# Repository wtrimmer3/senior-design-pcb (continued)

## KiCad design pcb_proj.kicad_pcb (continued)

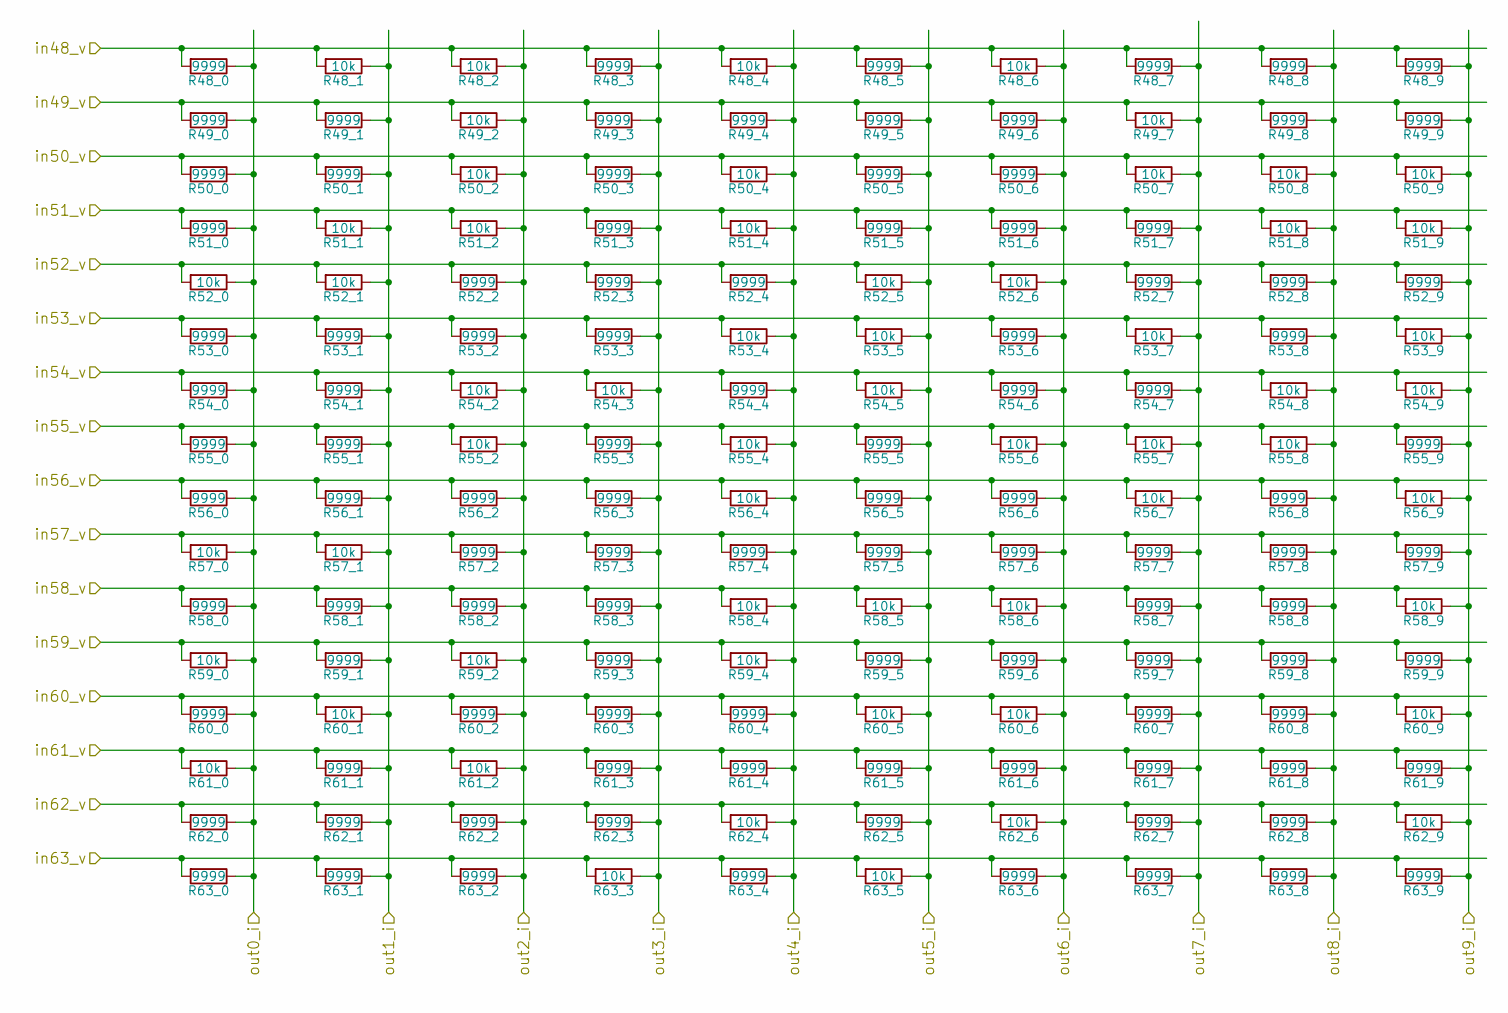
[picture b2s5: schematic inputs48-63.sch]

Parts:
R48_0, R48_3, R48_5, R48_7, R48_8, R48_9, R49_0, R49_1, R49_3, R49_4, R49_5, R49_6, R49_8, R49_9, R50_0, R50_1, R50_3, R50_5, R50_6, R51_0, R51_3, R51_5, R51_6, R51_7, R52_2, R52_3, R52_4, R52_7, R52_8, R52_9, R53_0, R53_1, R53_2, R53_3, R53_6, R53_8, R54_0, R54_1, R54_4, R54_6, R54_7, R55_0, R55_1, R55_3, R55_5, R55_9, R56_0, R56_1, R56_2, R56_3, R56_5, R56_6, R56_8, R57_2, R57_3, R57_4, R57_5, R57_6, R57_7, R57_8, R57_9, R58_0, R58_1, R58_2, R58_3, R58_7, R58_8, R59_1, R59_3, R59_5, R59_6, R59_7, R59_8, R59_9, R60_0, R60_2, R60_3, R60_4, R60_7, R60_8, R61_1, R61_3, R61_4, R61_5, R61_6, R61_7, R61_8, R61_9, R62_0, R62_1, R62_2, R62_3, R62_5, R62_7, R62_8, R63_0, R63_1, R63_2, R63_4, R63_6, R63_7, R63_8, R63_9: 9999
R48_1, R48_2, R48_4, R48_6, R49_2, R49_7, R50_2, R50_4, R50_7, R50_8, R50_9, R51_1, R51_2, R51_4, R51_8, R51_9, R52_0, R52_1, R52_5, R52_6, R53_4, R53_5, R53_7, R53_9, R54_2, R54_3, R54_5, R54_8, R54_9, R55_2, R55_4, R55_6, R55_7, R55_8, R56_4, R56_7, R56_9, R57_0, R57_1, R58_4, R58_5, R58_6, R58_9, R59_0, R59_2, R59_4, R60_1, R60_5, R60_6, R60_9, R61_0, R61_2, R62_4, R62_6, R62_9, R63_3, R63_5: 10k

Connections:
/C48: R48_0.2, R48_1.2, R48_2.2, R48_3.2, R48_4.2, R48_5.2, R48_6.2, R48_7.2, R48_8.2, R48_9.2; also elsewhere on the board
/C49: R49_0.2, R49_1.2, R49_2.2, R49_3.2, R49_4.2, R49_5.2, R49_6.2, R49_7.2, R49_8.2, R49_9.2; also elsewhere on the board
/C50: R50_0.2, R50_1.2, R50_2.2, R50_3.2, R50_4.2, R50_5.2, R50_6.2, R50_7.2, R50_8.2, R50_9.2; also elsewhere on the board
/C51: R51_0.2, R51_1.2, R51_2.2, R51_3.2, R51_4.2, R51_5.2, R51_6.2, R51_7.2, R51_8.2, R51_9.2; also elsewhere on the board
/C52: R52_0.2, R52_1.2, R52_2.2, R52_3.2, R52_4.2, R52_5.2, R52_6.2, R52_7.2, R52_8.2, R52_9.2; also elsewhere on the board
/C53: R53_0.2, R53_1.2, R53_2.2, R53_3.2, R53_4.2, R53_5.2, R53_6.2, R53_7.2, R53_8.2, R53_9.2; also elsewhere on the board
/C54: R54_0.2, R54_1.2, R54_2.2, R54_3.2, R54_4.2, R54_5.2, R54_6.2, R54_7.2, R54_8.2, R54_9.2; also elsewhere on the board
/C55: R55_0.2, R55_1.2, R55_2.2, R55_3.2, R55_4.2, R55_5.2, R55_6.2, R55_7.2, R55_8.2, R55_9.2; also elsewhere on the board
/C56: R56_0.2, R56_1.2, R56_2.2, R56_3.2, R56_4.2, R56_5.2, R56_6.2, R56_7.2, R56_8.2, R56_9.2; also elsewhere on the board
/C57: R57_0.2, R57_1.2, R57_2.2, R57_3.2, R57_4.2, R57_5.2, R57_6.2, R57_7.2, R57_8.2, R57_9.2; also elsewhere on the board
/C58: R58_0.2, R58_1.2, R58_2.2, R58_3.2, R58_4.2, R58_5.2, R58_6.2, R58_7.2, R58_8.2, R58_9.2; also elsewhere on the board
/C59: R59_0.2, R59_1.2, R59_2.2, R59_3.2, R59_4.2, R59_5.2, R59_6.2, R59_7.2, R59_8.2, R59_9.2; also elsewhere on the board
/C60: R60_0.2, R60_1.2, R60_2.2, R60_3.2, R60_4.2, R60_5.2, R60_6.2, R60_7.2, R60_8.2, R60_9.2; also elsewhere on the board
/C61: R61_0.2, R61_1.2, R61_2.2, R61_3.2, R61_4.2, R61_5.2, R61_6.2, R61_7.2, R61_8.2, R61_9.2; also elsewhere on the board
/C62: R62_0.2, R62_1.2, R62_2.2, R62_3.2, R62_4.2, R62_5.2, R62_6.2, R62_7.2, R62_8.2, R62_9.2; also elsewhere on the board
/C63: R63_0.2, R63_1.2, R63_2.2, R63_3.2, R63_4.2, R63_5.2, R63_6.2, R63_7.2, R63_8.2, R63_9.2; also elsewhere on the board
/resistor_network/OUT0: R48_0.1, R49_0.1, R50_0.1, R51_0.1, R52_0.1, R53_0.1, R54_0.1, R55_0.1, R56_0.1, R57_0.1, R58_0.1, R59_0.1, R60_0.1, R61_0.1, R62_0.1, R63_0.1; also elsewhere on the board
/resistor_network/OUT1: R48_1.1, R49_1.1, R50_1.1, R51_1.1, R52_1.1, R53_1.1, R54_1.1, R55_1.1, R56_1.1, R57_1.1, R58_1.1, R59_1.1, R60_1.1, R61_1.1, R62_1.1, R63_1.1; also elsewhere on the board
/resistor_network/OUT2: R48_2.1, R49_2.1, R50_2.1, R51_2.1, R52_2.1, R53_2.1, R54_2.1, R55_2.1, R56_2.1, R57_2.1, R58_2.1, R59_2.1, R60_2.1, R61_2.1, R62_2.1, R63_2.1; also elsewhere on the board
/resistor_network/OUT3: R48_3.1, R49_3.1, R50_3.1, R51_3.1, R52_3.1, R53_3.1, R54_3.1, R55_3.1, R56_3.1, R57_3.1, R58_3.1, R59_3.1, R60_3.1, R61_3.1, R62_3.1, R63_3.1; also elsewhere on the board
/resistor_network/OUT4: R48_4.1, R49_4.1, R50_4.1, R51_4.1, R52_4.1, R53_4.1, R54_4.1, R55_4.1, R56_4.1, R57_4.1, R58_4.1, R59_4.1, R60_4.1, R61_4.1, R62_4.1, R63_4.1; also elsewhere on the board
/resistor_network/OUT5: R48_5.1, R49_5.1, R50_5.1, R51_5.1, R52_5.1, R53_5.1, R54_5.1, R55_5.1, R56_5.1, R57_5.1, R58_5.1, R59_5.1, R60_5.1, R61_5.1, R62_5.1, R63_5.1; also elsewhere on the board
/resistor_network/OUT6: R48_6.1, R49_6.1, R50_6.1, R51_6.1, R52_6.1, R53_6.1, R54_6.1, R55_6.1, R56_6.1, R57_6.1, R58_6.1, R59_6.1, R60_6.1, R61_6.1, R62_6.1, R63_6.1; also elsewhere on the board
/resistor_network/OUT7: R48_7.1, R49_7.1, R50_7.1, R51_7.1, R52_7.1, R53_7.1, R54_7.1, R55_7.1, R56_7.1, R57_7.1, R58_7.1, R59_7.1, R60_7.1, R61_7.1, R62_7.1, R63_7.1; also elsewhere on the board
/resistor_network/OUT8: R48_8.1, R49_8.1, R50_8.1, R51_8.1, R52_8.1, R53_8.1, R54_8.1, R55_8.1, R56_8.1, R57_8.1, R58_8.1, R59_8.1, R60_8.1, R61_8.1, R62_8.1, R63_8.1; also elsewhere on the board
/resistor_network/OUT9: R48_9.1, R49_9.1, R50_9.1, R51_9.1, R52_9.1, R53_9.1, R54_9.1, R55_9.1, R56_9.1, R57_9.1, R58_9.1, R59_9.1, R60_9.1, R61_9.1, R62_9.1, R63_9.1; also elsewhere on the board

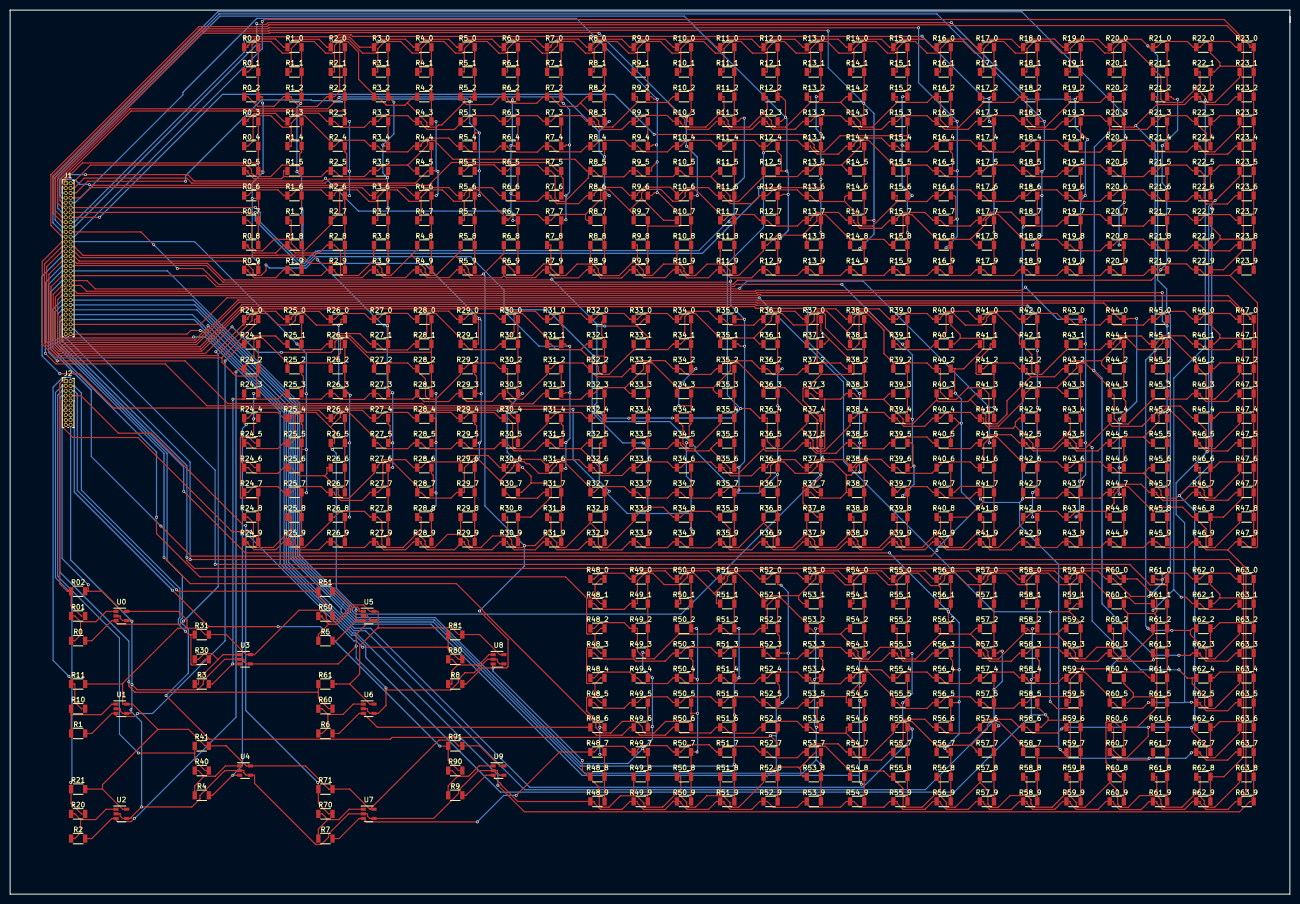
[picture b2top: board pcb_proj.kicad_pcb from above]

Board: 2 copper layers, 262.9 x 181.6 mm, 682 parts (0 on the bottom side), 96 nets.

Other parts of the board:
J1: Conn_02x32_Top_Bottom; PinHeader_2x32_P1.00mm_Vertical
J2: Conn_02x10_Top_Bottom; PinHeader_2x10_P1.00mm_Vertical

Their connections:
/C0: J1.1; also elsewhere on the board
/C1: J1.2; also elsewhere on the board
/C2: J1.3; also elsewhere on the board
/C3: J1.4; also elsewhere on the board
/C4: J1.5; also elsewhere on the board
/C5: J1.6; also elsewhere on the board
/C6: J1.7; also elsewhere on the board
/C7: J1.8; also elsewhere on the board
/C8: J1.9; also elsewhere on the board
/C9: J1.10; also elsewhere on the board
/C10: J1.11; also elsewhere on the board
/C11: J1.12; also elsewhere on the board
/C12: J1.13; also elsewhere on the board
/C13: J1.14; also elsewhere on the board
/C14: J1.15; also elsewhere on the board
/C15: J1.16; also elsewhere on the board
/C16: J1.17; also elsewhere on the board
/C17: J1.18; also elsewhere on the board
/C18: J1.19; also elsewhere on the board
/C19: J1.20; also elsewhere on the board
/C20: J1.21; also elsewhere on the board
/C21: J1.22; also elsewhere on the board
/C22: J1.23; also elsewhere on the board
/C23: J1.24; also elsewhere on the board
/C24: J1.25; also elsewhere on the board
/C25: J1.26; also elsewhere on the board
/C26: J1.27; also elsewhere on the board
/C27: J1.28; also elsewhere on the board
/C28: J1.29; also elsewhere on the board
/C29: J1.30; also elsewhere on the board
/C30: J1.31; also elsewhere on the board
/C31: J1.32; also elsewhere on the board
/C32: J1.33; also elsewhere on the board
/C33: J1.34; also elsewhere on the board
/C34: J1.35; also elsewhere on the board
/C35: J1.36; also elsewhere on the board
/C36: J1.37; also elsewhere on the board
/C37: J1.38; also elsewhere on the board
/C38: J1.39; also elsewhere on the board
/C39: J1.40; also elsewhere on the board
/C40: J1.41; also elsewhere on the board
/C41: J1.42; also elsewhere on the board
/C42: J1.43; also elsewhere on the board
/C43: J1.44; also elsewhere on the board
/C44: J1.45; also elsewhere on the board
/C45: J1.46; also elsewhere on the board
/C46: J1.47; also elsewhere on the board
/C47: J1.48; also elsewhere on the board
/C48: J1.49; also elsewhere on the board
/C49: J1.50; also elsewhere on the board
/C50: J1.51; also elsewhere on the board
/C51: J1.52; also elsewhere on the board
/C52: J1.53; also elsewhere on the board
/C53: J1.54; also elsewhere on the board
/C54: J1.55; also elsewhere on the board
/C55: J1.56; also elsewhere on the board
/C56: J1.57; also elsewhere on the board
/C57: J1.58; also elsewhere on the board
/C58: J1.59; also elsewhere on the board
/C59: J1.60; also elsewhere on the board
/C60: J1.61; also elsewhere on the board
/C61: J1.62; also elsewhere on the board
/C62: J1.63; also elsewhere on the board
/C63: J1.64; also elsewhere on the board
/op_amps/out0_v: J2.1; also elsewhere on the board
/op_amps/out1_v: J2.2; also elsewhere on the board
/op_amps/out2_v: J2.3; also elsewhere on the board
/op_amps/out3_v: J2.4; also elsewhere on the board
/op_amps/out4_v: J2.5; also elsewhere on the board
/op_amps/out5_v: J2.6; also elsewhere on the board
/op_amps/out6_v: J2.7; also elsewhere on the board
/op_amps/out7_v: J2.8; also elsewhere on the board
/op_amps/out8_v: J2.9; also elsewhere on the board
/op_amps/out9_v: J2.10; also elsewhere on the board
GND: J2.14, J2.15, J2.16, J2.17, J2.18, J2.19, J2.20; also elsewhere on the board
VDD: J2.11, J2.12, J2.13; also elsewhere on the board

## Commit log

2019-02-10 First Commit
    Created basic files for PCB design in KiCAD
2019-02-10 file
2019-02-10 Testing OS Differences
    Yay
2019-02-19 Mi-work push
    Started dropping in the op-amps, still work in progress.
2019-02-19 About to make a heirarchy, committing first in case we need to go back
2019-02-19 Start of Heirarchy
    Placed the Op Amps into their own block (still need to 'hook up' output pins). Created block for resistor network.
2019-02-22 Additional Heirarchy Changes
    Added resistor pages, still need to update values on them. See weight matrix file.
2019-02-23 updated labels for schematics 32-47 and 48-63
2019-02-24 added input/output for 16-31
2019-02-26 added labels
2019-02-26 added wires from input to output
2019-02-26 added labels and wires for rest of resistors
2019-02-27 added output wires
2019-03-01 Added some wires
    Added some wires, placed some terminals. Just a little bit of work.
2019-03-01 added resistor values for in0_v
2019-03-01 finised resistor values for inputs0-15
2019-03-02 finished inputs0-15
2019-03-02 added 10k to respective position
2019-03-02 added resistor values for 16-31
2019-03-02 added references for some resistors
2019-03-05 Updated resistors 32-63
2019-03-05 finished resistors0-31
2019-03-11 Finished Resistors 32-47
    Still need to finish naming 48-63
2019-03-11 Finished R48-R63
    Now to do the connector and provide power to the op amps
2019-03-25 Added footprints, finished schematic, began PCB layout
2019-03-29 fixed resistor schematic errors
2019-03-29 fixed all ERC errors
2019-04-02 Circuit complete
    Committing before I read in netlist just in case things get screwed
2019-04-02 Additional wires on PCB
2019-04-03 Commit before Auto-Routing
    Because this tool *might* just fuck everything up, so I want a "shit go back" point
2019-04-04 Commit after auto-routing
    It worked pretty well actually. Hell yeah.
2019-04-04 Commit post-autoroute
    Something weird happened in github so I think this should be the same commit
2019-04-04 Post Auto-Route Commit
    Deleted all the traces, then let the autorouter do its thing. It worked really well actually, so we'll probably just keep this.
2019-04-05 Generating gerber and drill files
    Probably need these for fab
2019-04-12 Commit with Plane
    Added some copper planes to make the etching process go faster
2019-04-14 Commit with new and improved copper planes
    Didn't commit gbr files that ended up being really really big
2019-04-17 Designed Mini-Board
    Slapped together a breakout board that has just the Op Amps and their resistors. It should work just fine
